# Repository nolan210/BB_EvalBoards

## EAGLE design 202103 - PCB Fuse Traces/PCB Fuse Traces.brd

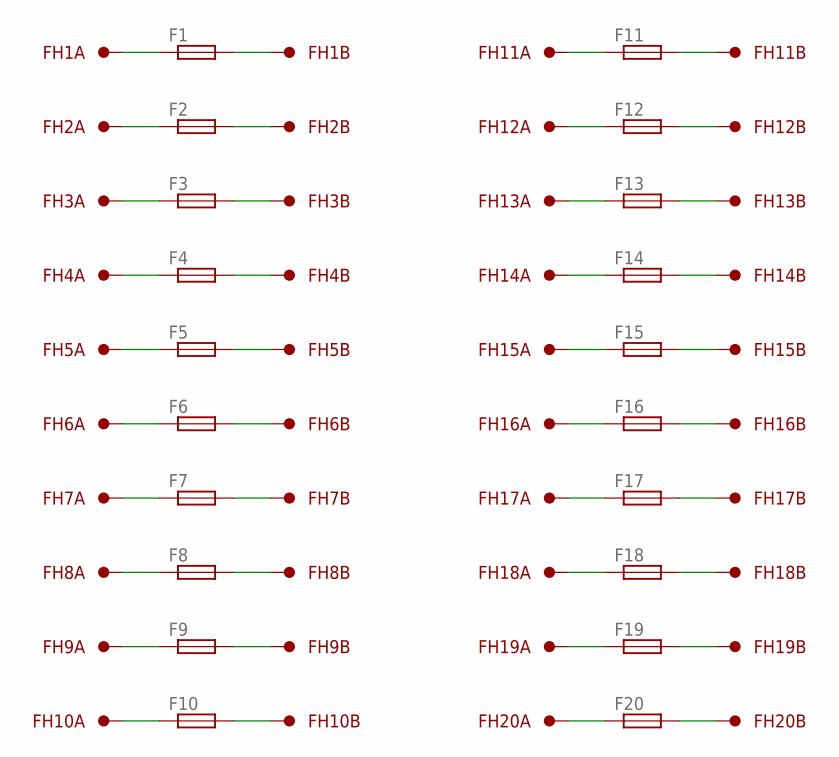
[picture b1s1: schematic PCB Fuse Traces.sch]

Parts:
F1: FUSEA; FUSE_A
F2: FUSEAA; FUSE_AA
F3: FUSEAAA; FUSE_AAA
F4: FUSEAAAA; FUSE_AAAA
F5: FUSEB; FUSE_B
F6: FUSEBB; FUSE_BB
F7: FUSEC; FUSE_C
F8: FUSECC; FUSE_CC
F9: FUSED; FUSE_D
F10: FUSEDD; FUSE_DD
F11: FUSEA0; FUSE_A0
F12: FUSEA1; FUSE_A1
F13: FUSEA3; FUSE_A3
F14: FUSEB1; FUSE_B1
F15: FUSEB2; FUSE_B2
F16: FUSEB3; FUSE_B3
F17: FUSEB4; FUSE_B4
F18: FUSE1206; F1206
F19: FUSE0805; F0805
F20: FUSE0603; F0603
FH1, FH2, FH3, FH4, FH5, FH6, FH7, FH8, FH9, FH10, FH11, FH12, FH13, FH14, FH15, FH16, FH17, FH18, FH19, FH20: FUSE_HOLDER36MM; F36_HOLDER

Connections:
unnamed: F1.1, FH1.1
unnamed: F2.1, FH2.1
unnamed: F3.1, FH3.1
unnamed: F4.1, FH4.1
unnamed: F1.2, FH1.2
unnamed: F2.2, FH2.2
unnamed: F3.2, FH3.2
unnamed: F4.2, FH4.2
unnamed: F5.1, FH5.1
unnamed: F6.1, FH6.1
unnamed: F7.1, FH7.1
unnamed: F8.1, FH8.1
unnamed: F5.2, FH5.2
unnamed: F6.2, FH6.2
unnamed: F7.2, FH7.2
unnamed: F8.2, FH8.2
unnamed: F9.1, FH9.1
unnamed: F10.1, FH10.1
unnamed: F11.3 (1), FH11.1
unnamed: F12.1, FH12.1
unnamed: F9.2, FH9.2
unnamed: F10.2, FH10.2
unnamed: F11.4 (2), FH11.2
unnamed: F12.2, FH12.2
unnamed: F13.1, FH13.1
unnamed: F14.1, FH14.1
unnamed: F15.1, FH15.1
unnamed: F16.1, FH16.1
unnamed: F13.2, FH13.2
unnamed: F14.2, FH14.2
unnamed: F15.2, FH15.2
unnamed: F16.2, FH16.2
unnamed: F17.1, FH17.1
unnamed: F18.1, FH18.1
unnamed: F19.1, FH19.1
unnamed: F20.1, FH20.1
unnamed: F17.2, FH17.2
unnamed: F18.2, FH18.2
unnamed: F19.2, FH19.2
unnamed: F20.2, FH20.2

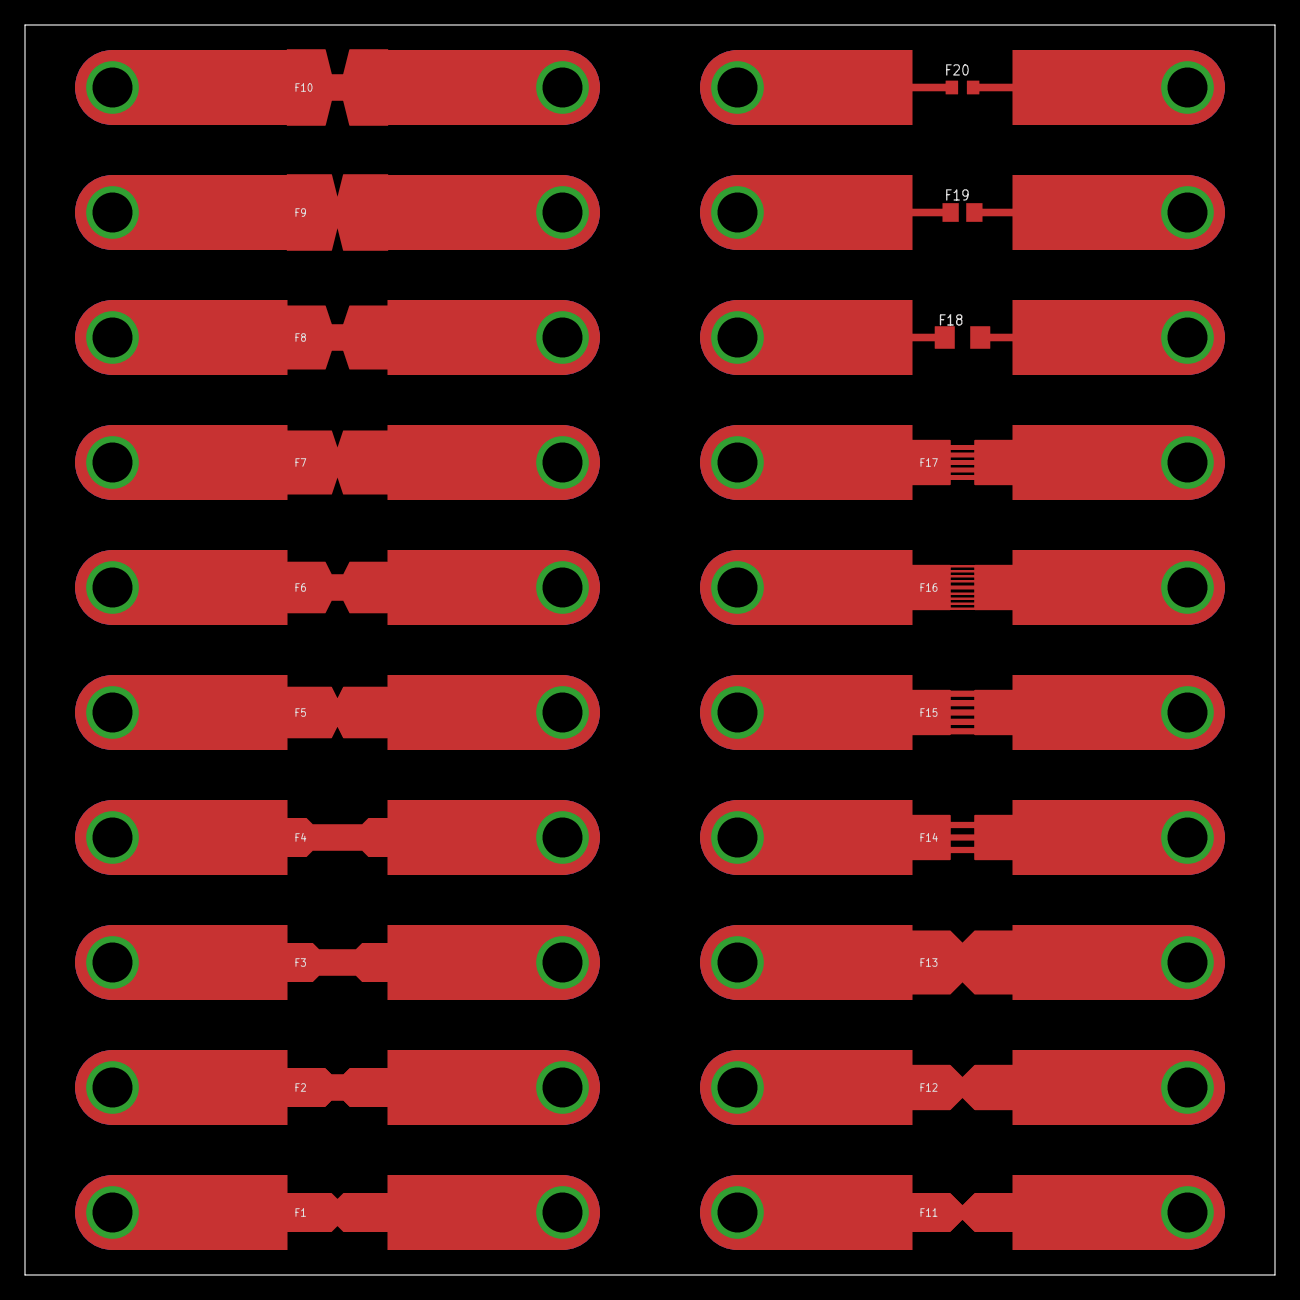
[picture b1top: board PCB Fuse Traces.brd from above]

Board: 2 copper layers, 100.0 x 100.0 mm, 40 parts (0 on the bottom side), 40 nets.

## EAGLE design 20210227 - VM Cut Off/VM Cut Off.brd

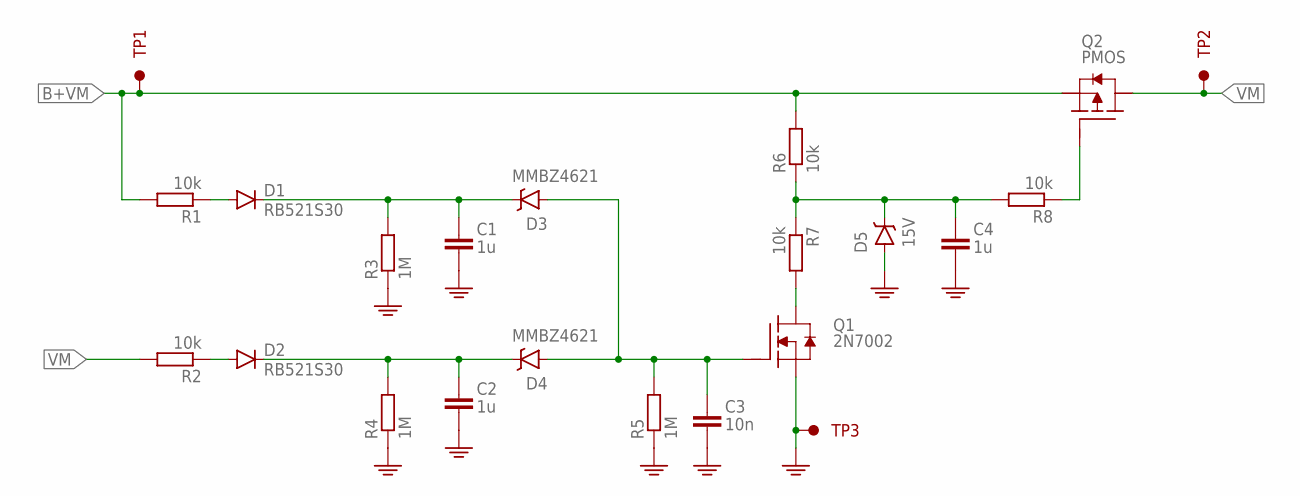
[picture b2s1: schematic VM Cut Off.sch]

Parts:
C1, C2, C4: 1u; C0402
C3: 10n; C0402
D1, D2: RB521S30; SC79_INFINEON
D3, D4: MMBZ4621; SOT23
D5: 15V; SOT23
Q1: 2N7002; SOT23
Q2: PMOS; SOT23
R1, R2, R6, R7, R8: 10k; R0402
R3, R4, R5: 1M; R0402
TP1: PWR; PINS_1_TESTPOINT_KE5000_NOTEXT
TP2: OUT; PINS_1_TESTPOINT_KE5000_NOTEXT
TP3: GND; PINS_1_TESTPOINT_KE5000_NOTEXT

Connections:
B+VM: Q2.3 (S), R1.2, R6.2, TP1.1
GND: C1.2, C2.2, C3.2, C4.2, D5.1 (A), Q1.2 (S), R3.1, R4.1, R5.1, TP3.1
unnamed: Q1.3 (D), R7.2
unnamed: Q2.1 (G), R8.1
unnamed: C4.1, D5.3 (C), R6.1, R7.1, R8.2
unnamed: C3.1, D3.1 (A), D4.1 (A), Q1.1 (G), R5.2
unnamed: C1.1, D1.C, D3.3 (C), R3.2
unnamed: D2.A, R2.1
unnamed: D1.A, R1.1
unnamed: C2.1, D2.C, D4.3 (C), R4.2
VM: Q2.2 (D), R2.2, TP2.1

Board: 2 copper layers, 22 parts (3 on the bottom side), 11 nets, no tracks yet.

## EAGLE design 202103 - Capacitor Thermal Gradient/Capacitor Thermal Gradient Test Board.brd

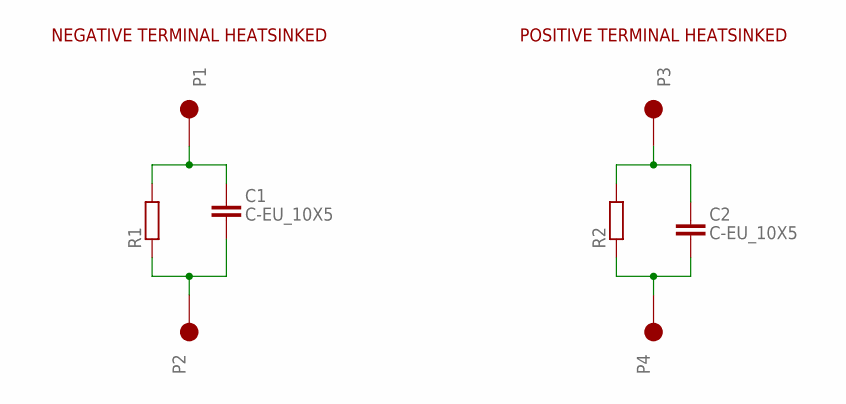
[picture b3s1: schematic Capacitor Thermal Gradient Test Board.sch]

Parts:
C1, C2: C-EU_10X5; C_PZF_10
P1, P2, P3, P4: PINS_1_2MM2
R1, R2: R-EU__VISHAY_THJP1225AST1; R_THERMAL_1225

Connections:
unnamed: C1.1+ (1), P1.1, R1.2
unnamed: C1.2- (2), P2.1, R1.1
unnamed: C2.1+ (1), P3.1, R2.2
unnamed: C2.2- (2), P4.1, R2.1

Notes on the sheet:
NEGATIVE TERMINAL HEATSINKED
POSITIVE TERMINAL HEATSINKED

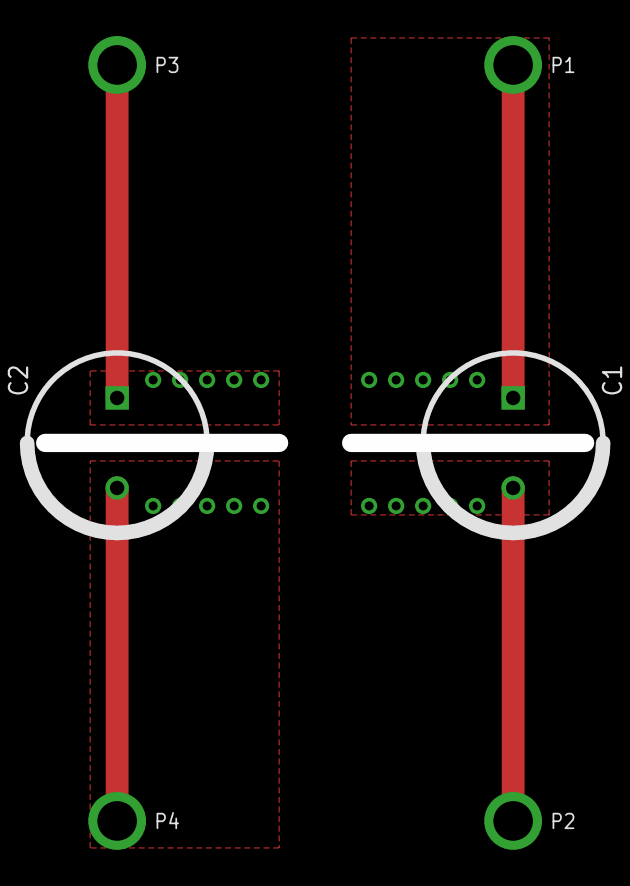
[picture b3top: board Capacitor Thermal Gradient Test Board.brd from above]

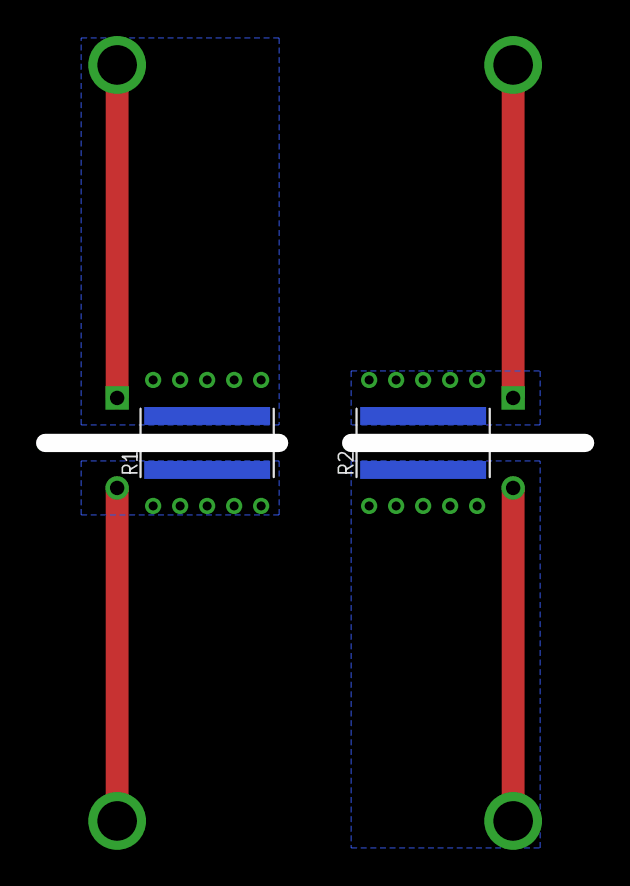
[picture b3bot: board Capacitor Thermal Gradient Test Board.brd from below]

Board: 2 copper layers, 8 parts (2 on the bottom side), 4 nets.

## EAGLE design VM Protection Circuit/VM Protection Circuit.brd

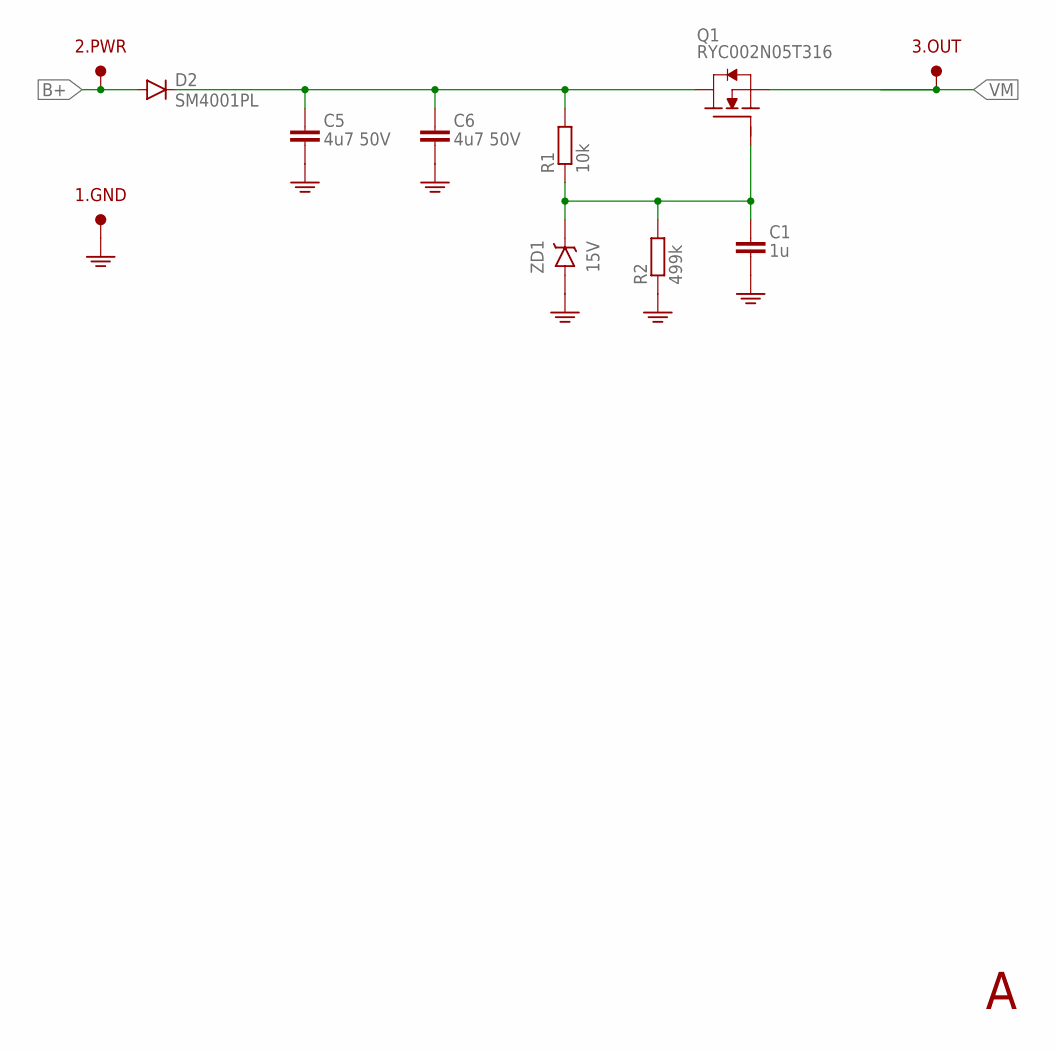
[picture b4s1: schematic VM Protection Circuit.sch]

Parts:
1.GND, 2.PWR, 3.OUT: TESTPOINTKE5000-SMTEXT; PINS_1_TESTPOINT_KE5000_NOTEXT
C1: 1u; C0402
C5, C6: 4u7 50V; C0805
D2: SM4001PL; SOD123
Q1: RYC002N05T316; SOT23
R1: 10k; R0402
R2: 499k; R0402
ZD1: 15V; SOT23

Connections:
B+: 2.PWR.1, D2.A
GND: 1.GND.1, C1.2, C5.2, C6.2, R2.1, ZD1.1 (A)
Q1.DRAIN: C5.1, C6.1, D2.C, Q1.3 (D), R1.2
Q1.GATE: C1.1, Q1.1 (G), R1.1, R2.2, ZD1.3 (C)
VM: 3.OUT.1, Q1.2 (S)

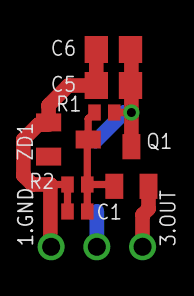
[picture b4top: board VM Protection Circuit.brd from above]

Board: 2 copper layers, 11 parts (1 on the bottom side), 5 nets.

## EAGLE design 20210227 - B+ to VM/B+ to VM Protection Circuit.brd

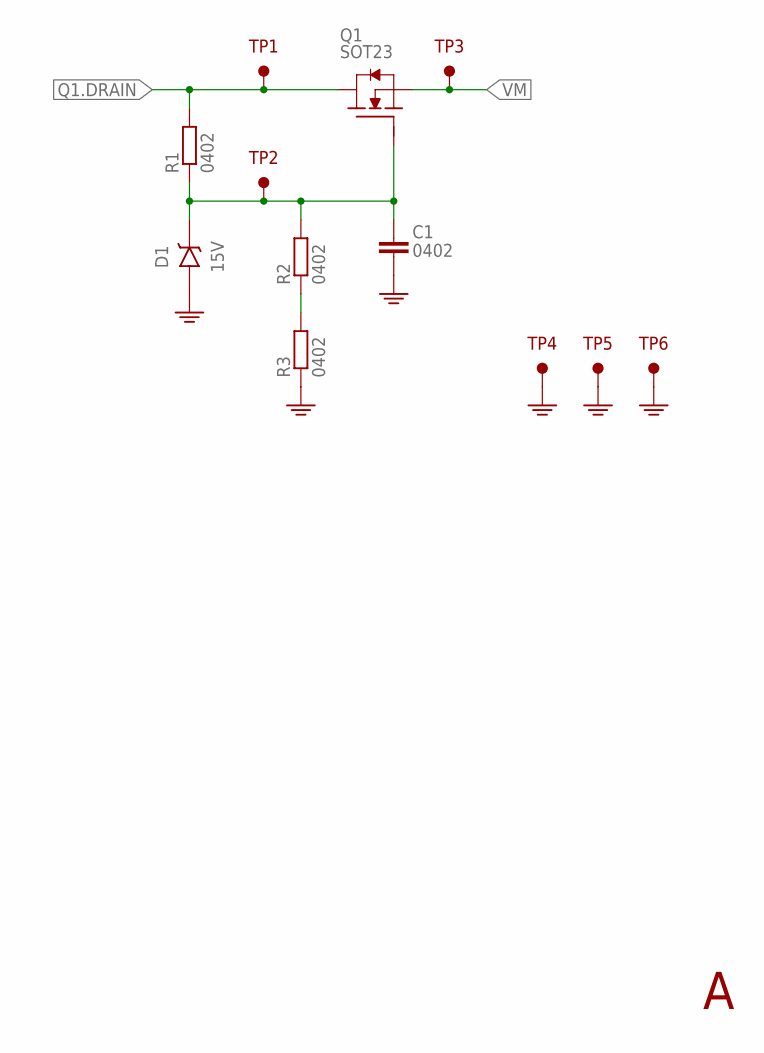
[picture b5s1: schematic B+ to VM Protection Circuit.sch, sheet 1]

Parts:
C1: 0402; C0402
D1: 15V; SOT23
Q1: SOT23
R1, R2, R3: 0402; R0402
TP1, TP2, TP3, TP4, TP5, TP6: TESTPOINTKE5000-SMTEXT; PINS_1_TESTPOINT_KE5000_NOTEXT

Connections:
GND: C1.2, D1.1 (A), R3.1, TP4.1, TP5.1, TP6.1; also elsewhere on the board
unnamed: R2.1, R3.2
Q1.DRAIN: Q1.3 (D), R1.2, TP1.1; also elsewhere on the board
Q1.GATE: C1.1, D1.3 (C), Q1.1 (G), R1.1, R2.2, TP2.1
VM: Q1.2 (S), TP3.1; also elsewhere on the board

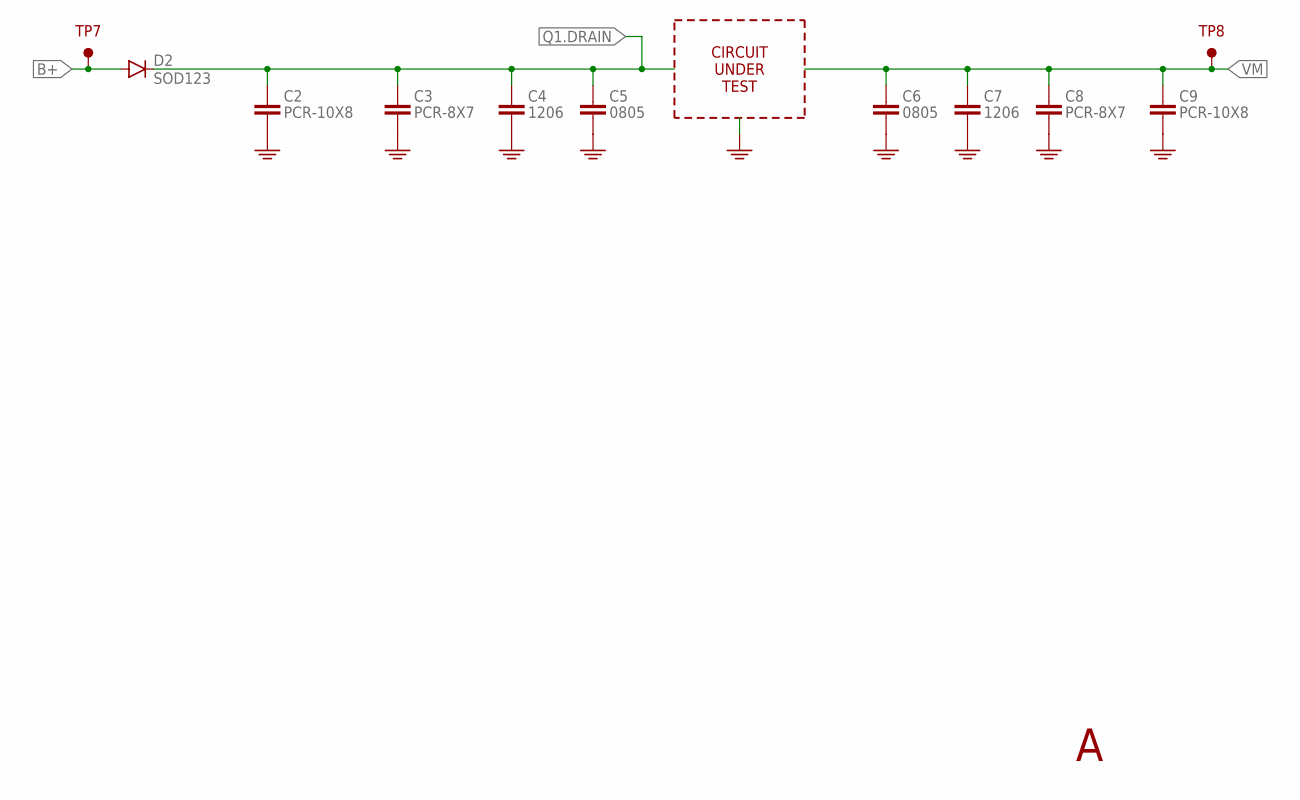
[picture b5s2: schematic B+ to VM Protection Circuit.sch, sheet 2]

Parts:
C2, C9: PCR-10X8; C-PCR-10X8
C3, C8: PCR-8X7; C-PCR-8X7
C4, C7: 1206; C1206
C5, C6: 0805; C0805
D2: SOD123
TP7, TP8: TESTPOINTKE5000-SMTEXT; PINS_1_TESTPOINT_KE5000_NOTEXT

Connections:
B+: D2.A, TP7.1; also elsewhere on the board
GND: C2.- (2), C3.- (2), C4.- (2), C5.2, C6.2, C7.- (2), C8.- (2), C9.- (2); also elsewhere on the board
Q1.DRAIN: C2.+ (1), C3.+ (1), C4.+ (1), C5.1, D2.C; also elsewhere on the board
VM: C6.1, C7.+ (1), C8.+ (1), C9.+ (1), TP8.1; also elsewhere on the board

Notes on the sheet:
CIRCUIT UNDER TEST

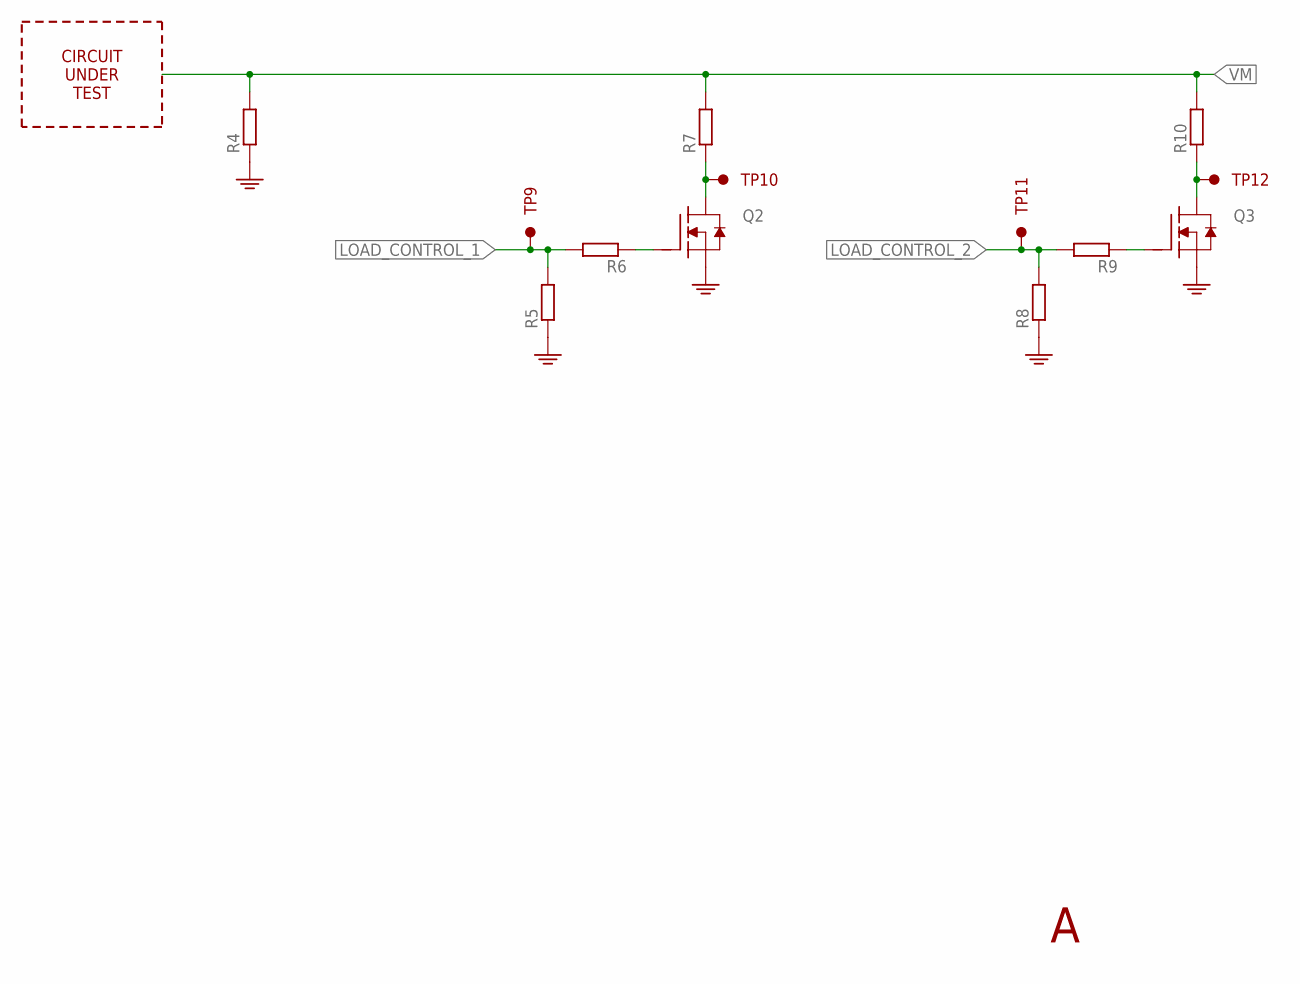
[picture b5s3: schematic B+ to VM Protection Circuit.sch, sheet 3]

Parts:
Q2, Q3: MOSFET-N_NTMFS5C426NT3G; DFN5
R4, R7, R10: R-EU_0207/10; 0207/10
R5, R6, R8, R9: R-EU_M0805; M0805
TP9, TP10, TP11, TP12: TESTPOINTKE5000-SMTEXT; PINS_1_TESTPOINT_KE5000_NOTEXT

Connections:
GND: Q2.1 (S), Q2.2 (S), Q2.3 (S), Q3.1 (S), Q3.2 (S), Q3.3 (S), R4.1, R5.1, R8.1; also elsewhere on the board
LOAD_CONTROL_1: R5.2, R6.2, TP9.1
LOAD_CONTROL_2: R8.2, R9.2, TP11.1
unnamed: Q2.5 (D), R7.1, TP10.1
unnamed: Q3.5 (D), R10.1, TP12.1
unnamed: Q3.4 (G), R9.1
unnamed: Q2.4 (G), R6.1
VM: R4.2, R7.2, R10.2; also elsewhere on the board

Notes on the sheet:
CIRCUIT UNDER TEST

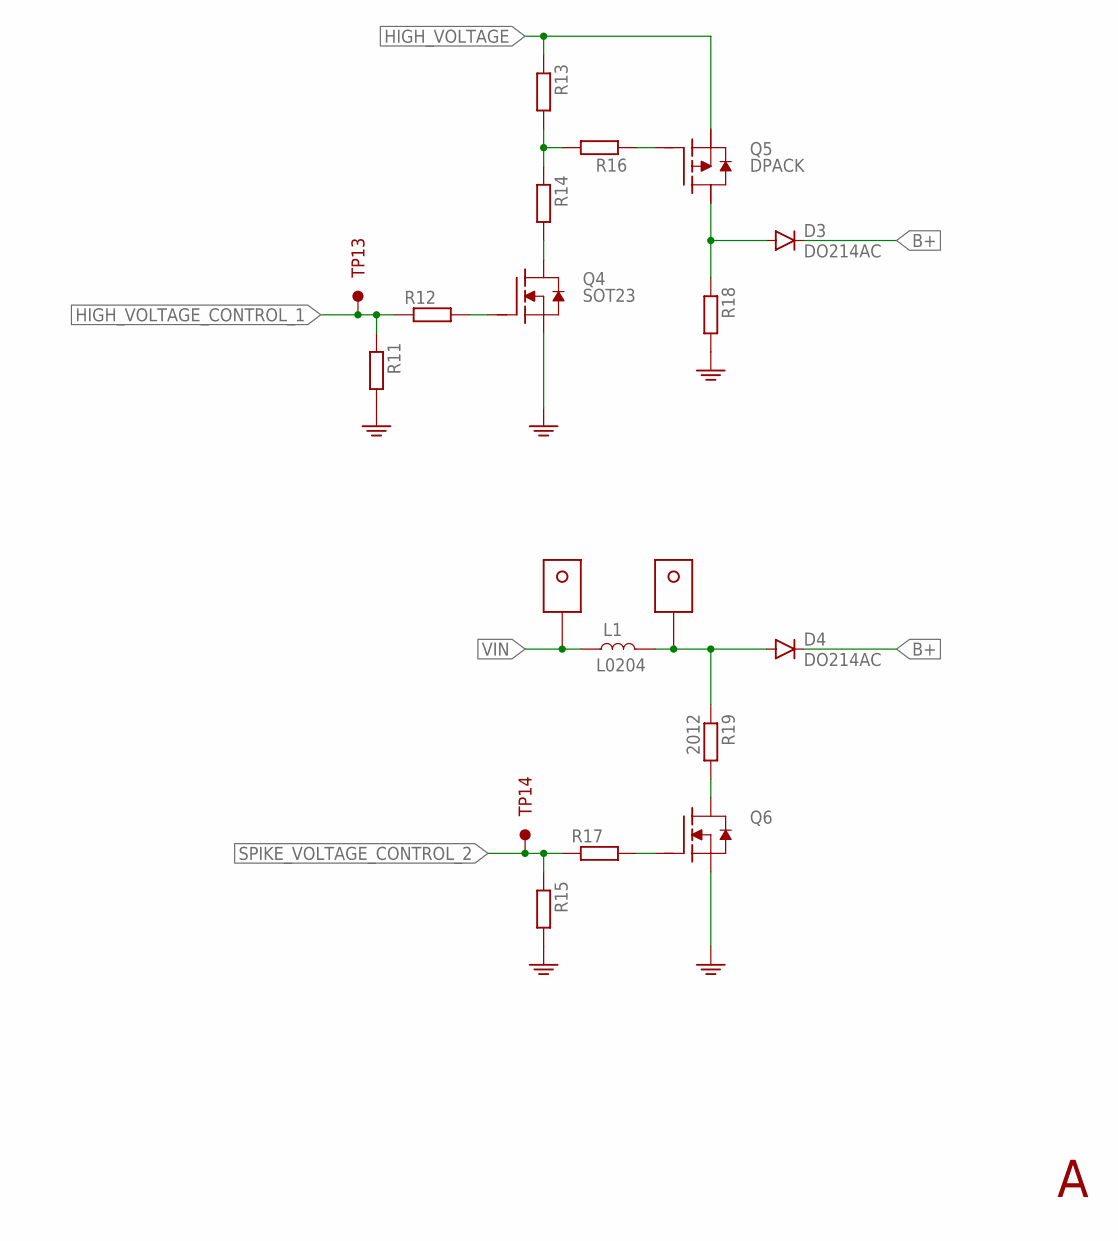
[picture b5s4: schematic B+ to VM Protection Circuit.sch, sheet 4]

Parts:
D3, D4: DO214AC
L1: L0204; 0204/5
Q4: SOT23
Q5: DPACK; D-PAK_TO252AA
Q6: MOSFET-N_NTMFS5C426NT3G; DFN5
R11, R12, R13, R14, R15, R16, R17, R18: R-EU_M0805; M0805
R19: 2012; R1210
TP13, TP14: TESTPOINTKE5000-SMTEXT; PINS_1_TESTPOINT_KE5000_NOTEXT
U$1, U$2: SPADE-TAB; SPADE-TAB-6.3MM

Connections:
B+: D3.C, D4.C; also elsewhere on the board
GND: Q4.2 (S), Q6.1 (S), Q6.2 (S), Q6.3 (S), R11.2, R15.2, R18.2; also elsewhere on the board
HIGH_VOLTAGE: Q5.4 (S), R13.1; also elsewhere on the board
HIGH_VOLTAGE_CONTROL_1: R11.1, R12.1, TP13.1
unnamed: R13.2, R14.1, R16.2
unnamed: Q4.1 (G), R12.2
unnamed: Q4.3 (D), R14.2
unnamed: D3.A, Q5.3 (D), R18.1
unnamed: Q6.4 (G), R17.2
unnamed: D4.A, L1.2, R19.1, U$2.P$1, U$2.P$2
unnamed: Q5.1 (G), R16.1
unnamed: Q6.5 (D), R19.2
SPIKE_VOLTAGE_CONTROL_2: R15.1, R17.1, TP14.1
VIN: L1.1, U$1.P$1, U$1.P$2; also elsewhere on the board

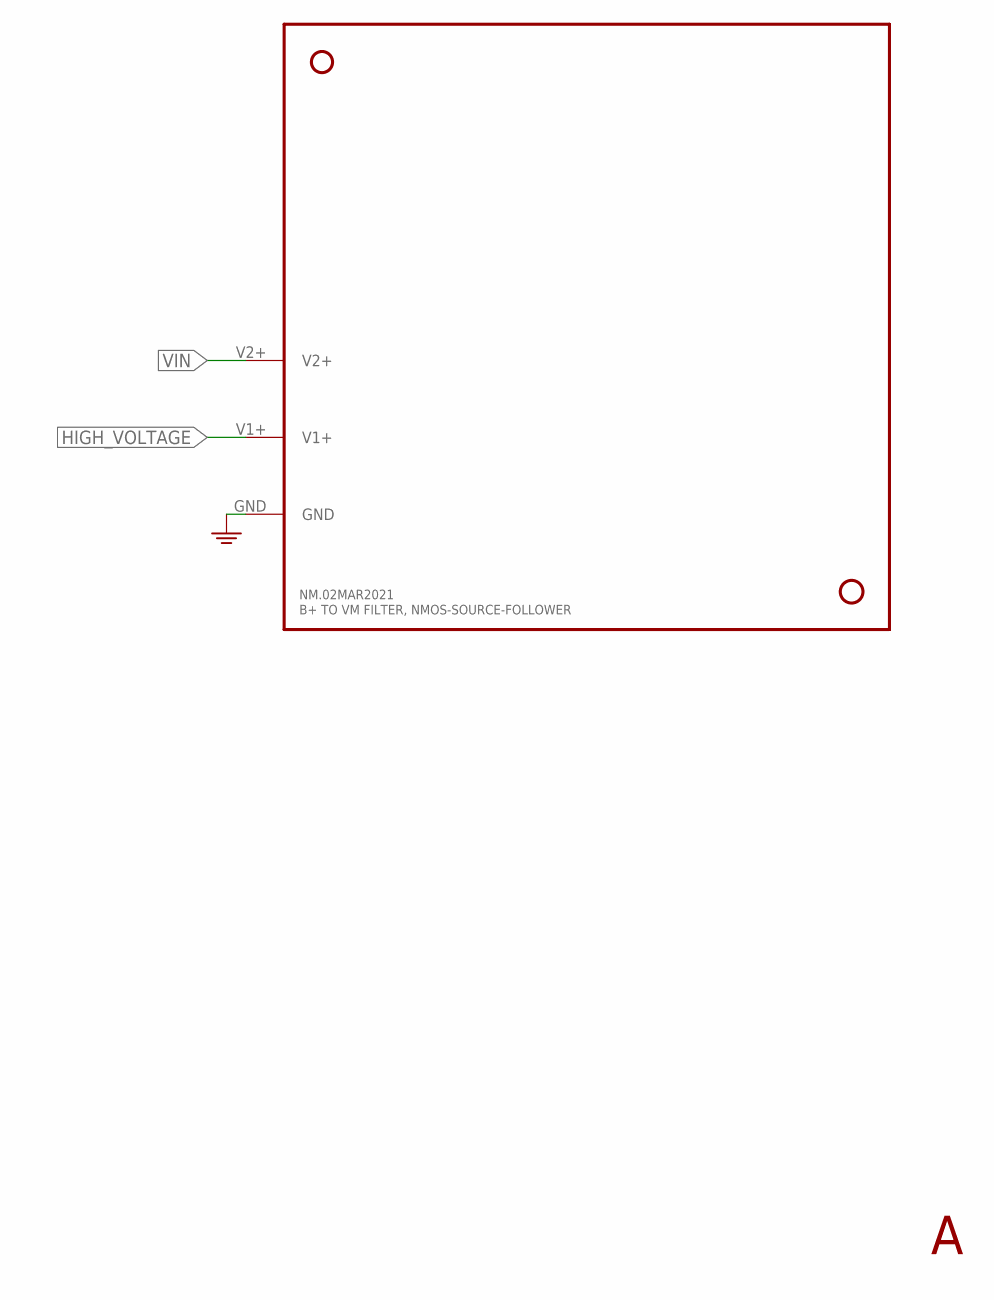
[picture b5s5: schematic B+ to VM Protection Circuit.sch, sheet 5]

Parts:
NM.02MAR2021: B+ TO VM FILTER, NMOS-SOURCE-FOLLOWER; EVAL-80X80

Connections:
GND: NM.02MAR2021.GND; also elsewhere on the board
HIGH_VOLTAGE: NM.02MAR2021.V1+; also elsewhere on the board
VIN: NM.02MAR2021.V2+; also elsewhere on the board

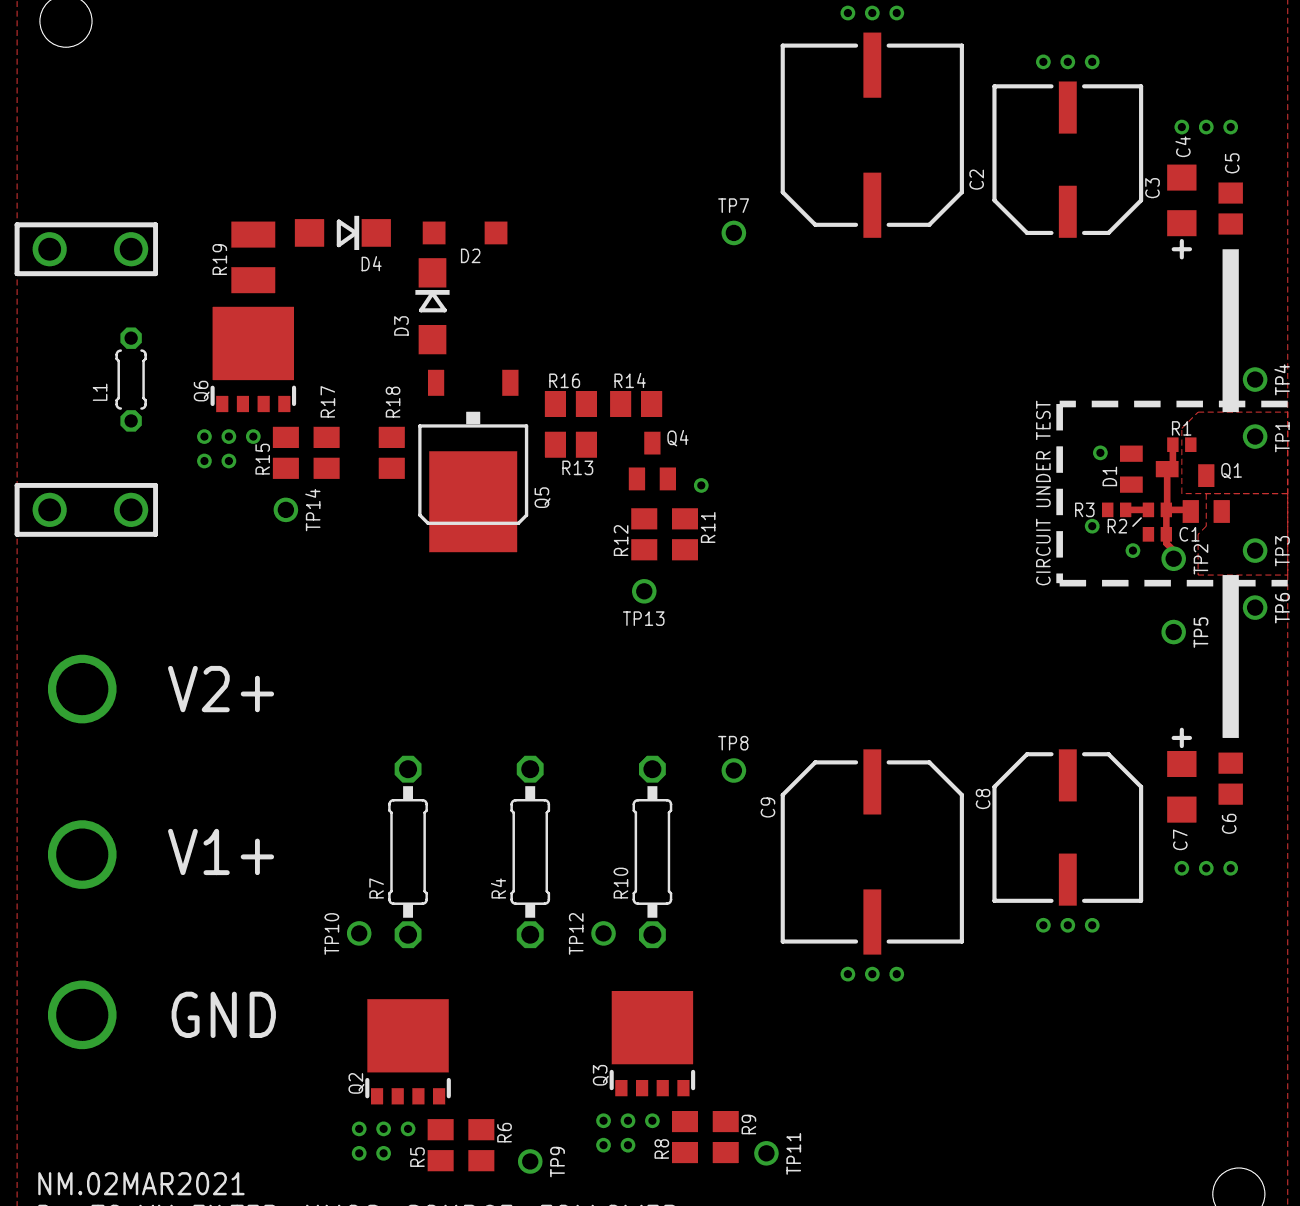
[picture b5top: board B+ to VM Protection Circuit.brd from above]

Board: 2 copper layers, 56 parts (0 on the bottom side), 24 nets.

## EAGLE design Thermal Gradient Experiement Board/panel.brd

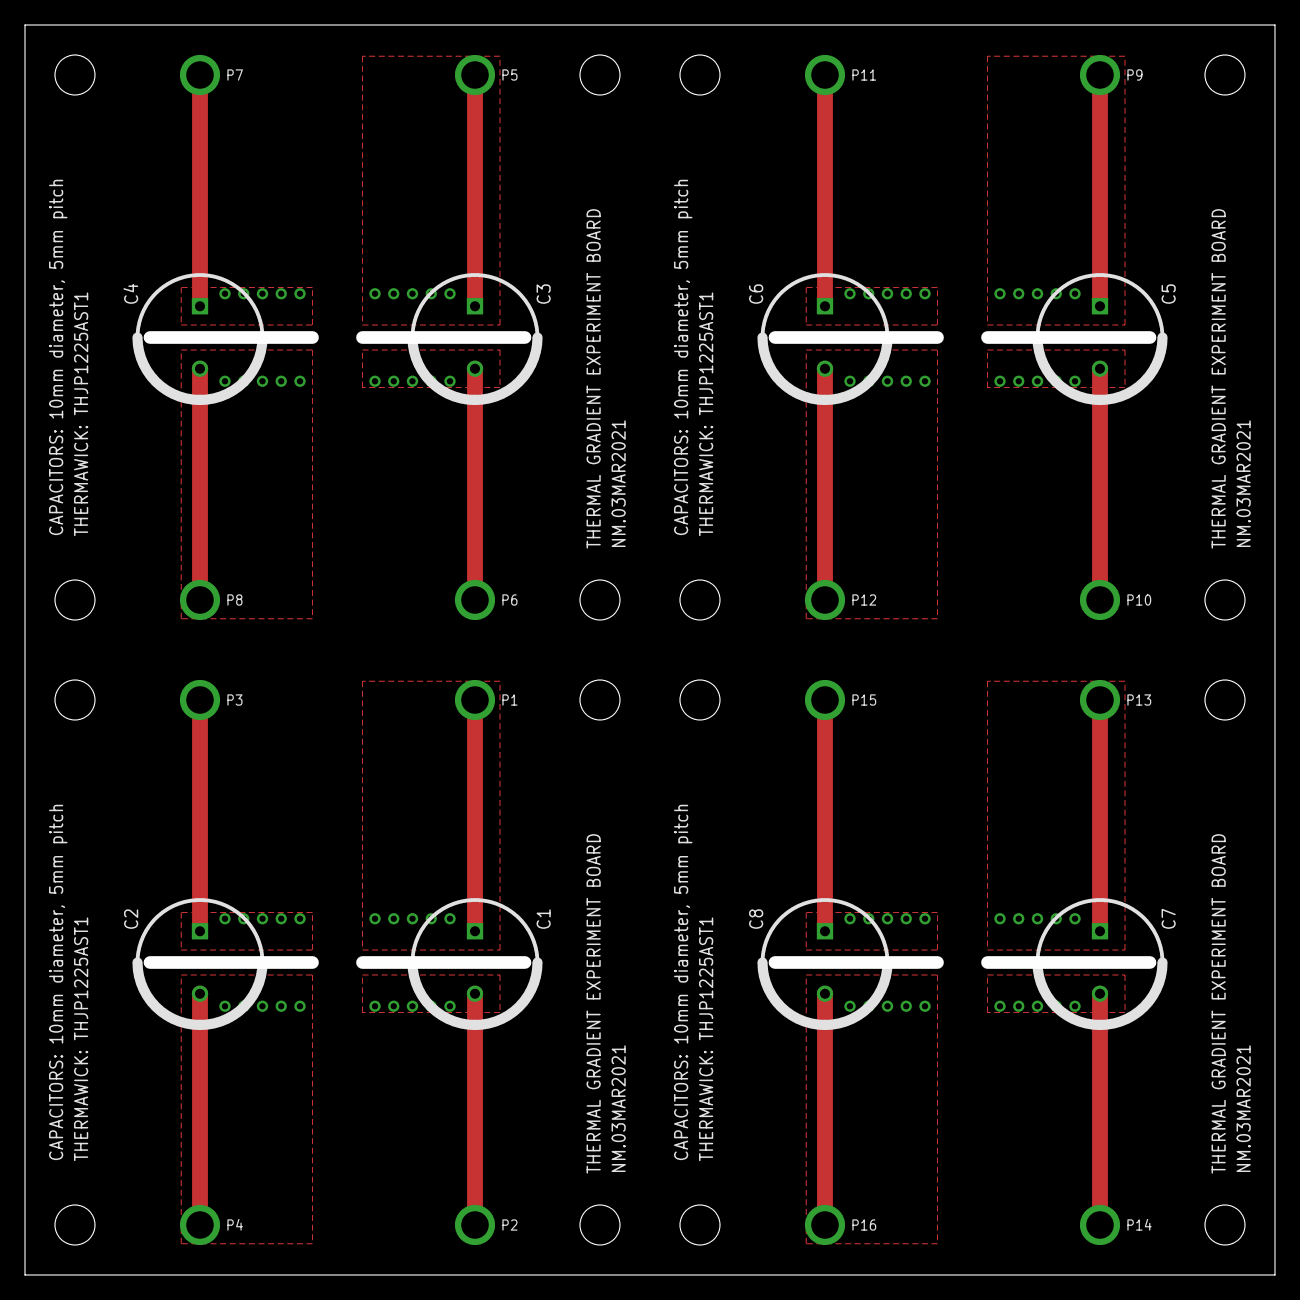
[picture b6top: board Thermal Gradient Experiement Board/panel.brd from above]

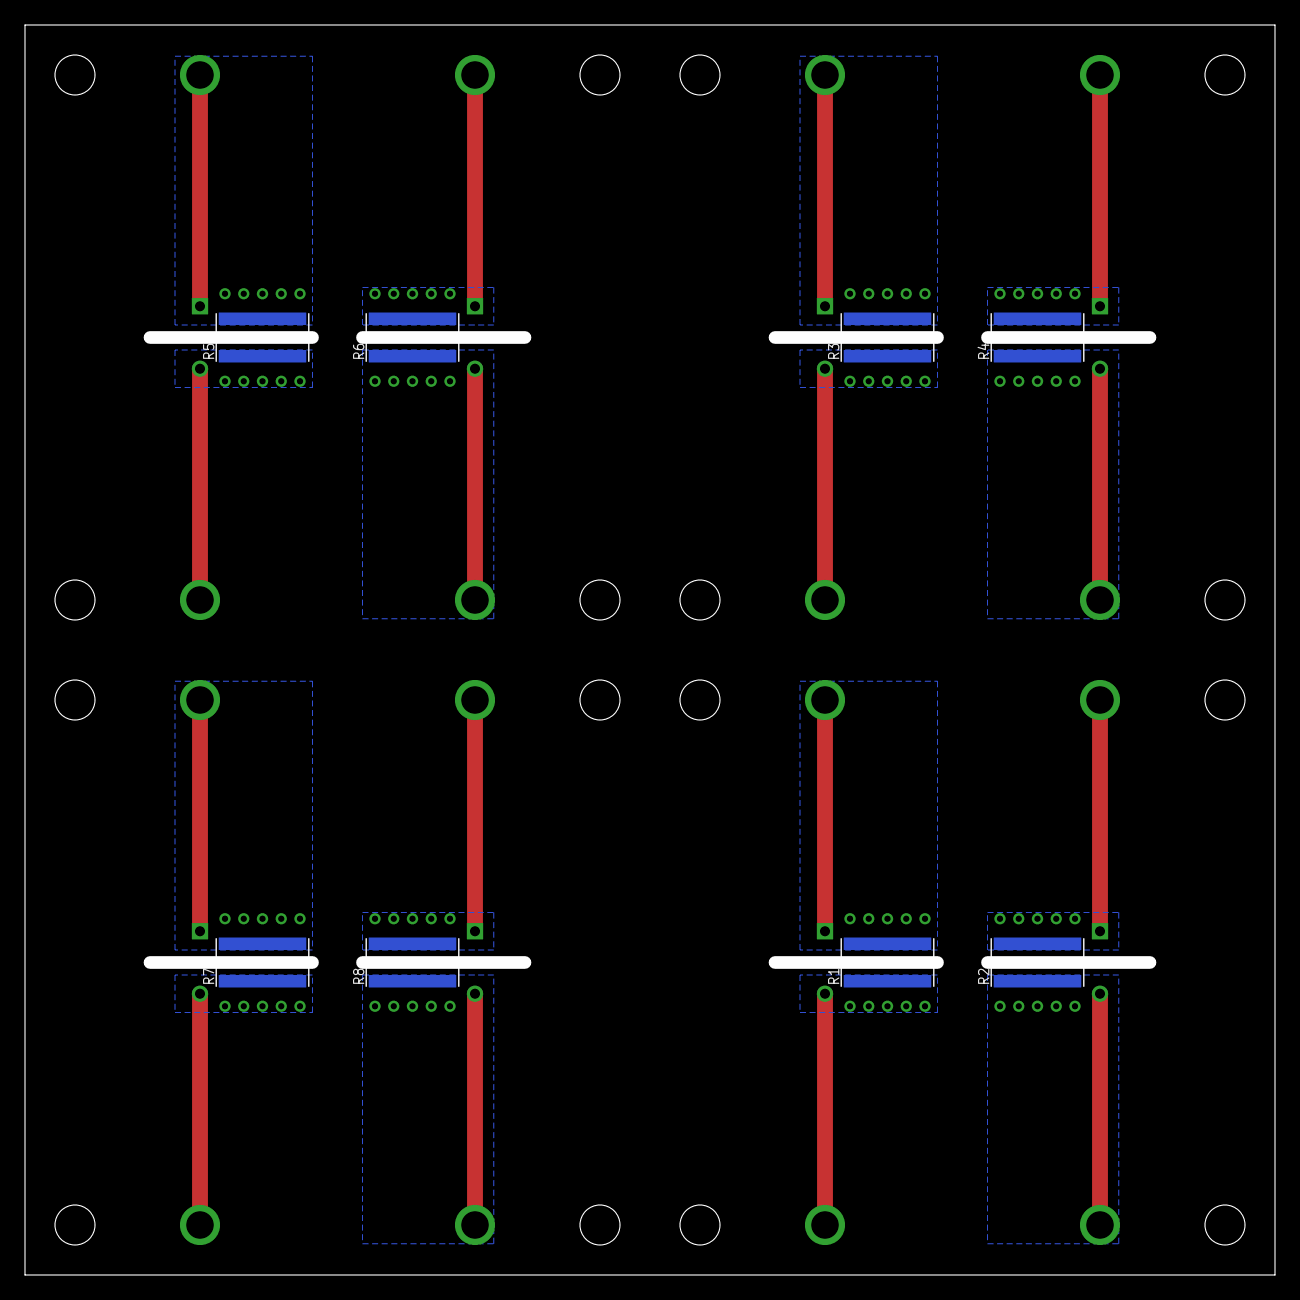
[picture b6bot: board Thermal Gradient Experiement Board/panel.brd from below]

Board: 2 copper layers, 100.0 x 100.0 mm, 32 parts (8 on the bottom side), 16 nets.

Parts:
C1, C2, C3, C4, C5, C6, C7, C8: C-EU_10X5; C_PZF_10
P1, P2, P3, P4, P5, P6, P7, P8, P9, P10, P11, P12, P13, P14, P15, P16: PINS_1_2MM2
R1, R2, R3, R4, R5, R6, R7, R8: R_THERMAL_1225

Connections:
unnamed: C1.1+, P1.1, R1.2
unnamed: C1.2-, P2.1, R1.1
unnamed: C2.1+, P3.1, R2.2
unnamed: C2.2-, P4.1, R2.1
unnamed: C3.1+, P5.1, R3.2
unnamed: C3.2-, P6.1, R3.1
unnamed: C4.1+, P7.1, R4.2
unnamed: C4.2-, P8.1, R4.1
unnamed: C5.1+, P9.1, R5.2
unnamed: C5.2-, P10.1, R5.1
unnamed: C6.1+, P11.1, R6.2
unnamed: C6.2-, P12.1, R6.1
unnamed: C7.1+, P13.1, R7.2
unnamed: C7.2-, P14.1, R7.1
unnamed: C8.1+, P15.1, R8.2
unnamed: C8.2-, P16.1, R8.1
